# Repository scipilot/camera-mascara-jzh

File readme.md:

This is a Raspberry Pi Hat for the "Camera Mascara" mark 2, containing a photodiode transimpedance amplifier and an ADC with a bunch of breakout options for experimenting with the gain and other parameters, like a dev board.

See the other two related repos: 

- https://github.com/scipilot/camera-mascara			(essential code for running the camera)
- https://github.com/scipilot/camera-mascara-vue-pocketbase 	(optional UI app)

## How to use

The circuit has options, but also fair defaults so you can just plug in a photodiode to J2, jump J4 pins 1-2 and jump J3 pins 1-2. 

The jumper options were intended to facilitate trialling different opamp designs not just passive values, while still using well-soldered SMD components, avoiding breadboard problems. There are many ways to feed a photodiode signal into an opamp, so I wanted to enable radical changes to the circuit - although probably could have done much better with a more open "protoboard" type layout. The default design is a transimpedance amplifier, where the photodiode reverse bias is also generated via the opamp as the negative feedback tries to keep the inverting input the same as the non-inverting input which itself is held at the bias level.

The default Rfb 10MΩ turned out to be too high (for the Hamamatsu diode I tried). But a 1.6MΩ pot on J3 (on pins 4-5, with pins 2-3 jumped) was very useful for various level experiments. Somewhere around 500kΩ is probably a good starting point.

The potentiometer option on J4 turned out not to be so useful, but installing R1 was more useful in setting the reverse bias of the photodiode. It depends on the photodiode, but keeping the bias as low as possible (while still performing its function) helps to keep the "black" output level down lower which was more compatible with the ADC (especially without the VIN-neg bias option) and allowing higher gain before clipping. I installed a 25kΩ R1 which leads to a 1V reverse bias, (25:100 divider of 5V on the Pi supply) which is safely above the 0.7V minimum reverse bias of the Hamamatsu diode.

The 0Ω links were also intended to be removable, but in reality it's pretty difficult at that size!

The opamp capacitors aren't so important these low frequencies - they are in the reference designs which are more concerned with high-frequency applications. Considering this ADC supports 15 to 240 samples per second, it's all running sub 1kHz.

Shielding the cable to the photosensor is important, which can be connected to Pin 1 of J2 and linked to GND. This significantly reduces mains hum, especially with higher amplification of very low light levels (single pixel mask).

The ADS1110 is IC2 addressed according to the variant, so e.g. ADS1110-ED0 is on address 0x48. The ADS1110 does not use registers so some standard tools don't work with it, as they commonly write a register address before reading which will overwrite the config of this chip. 

The ADS1110 has four possible differential ranges: -2V to +2V at PGA (gain) x1, down to -0.25 to +0.25V at PGA gain x8. 

Note: As we are measuring positive going signals (not AC or audio) but the ADC is differential, the input should to biased to the bottom of this range to enable us to use the full range. To do this you can supply 1V or 2V to the negative input. I did not facilitate this option in the first version of the schematic, and sadly routed the VIN-neg pin to the GND under the chip which made it difficult to amend (desolder chip and cut the track or lift the pin)! I have remedied this in v2 of the schematic (not manufactured yet). This bias could also be achieved in the output of the opamp or other ways, but the VIN-neg is the easiest.

TP1 is the most interesting signal to probe. Ensuring it's clean and not going to clip outside the range of the ADC is crucial. 

TP2 isn't really useful, as the signal is a current not voltage.  TP3 was used in experiments to record the PD rev-bias and its effect on the performance.

I added a bunch of other proto-board-like component positions and jumper/vias which are not on the schematic. These were useful to be able to hard-solder optional things like a 1V voltage divider for the VIN-neg ADC input (after cutting the strap to GND).

There were no TPs for the I2C for debugging which was annoying and will also be remedied in v2.

The components I chose were swayed by what was available at JLCPCB (or LCSC). The TIA is good, but I think the ADC could be better.

Next steps: v2 will have the prototyping amendments mentioned, plus possible a triple channel layout, for doing RGB images, or a dual-sensor for monitoring background light levels, and perhaps a different non-differential ADC or with less weird I2C. 

Also I forgot the GO button which could be used to take a picture, but the UI app seems more suitable for this, as there are resolution options and other config available. The GO button might be useful if the device settles down to be a point-and-shoot camera with less focus on endlessly tuning the circuit. At that time, I'd make a "production" board without so many the prototyping options. 

There currently is no case design.

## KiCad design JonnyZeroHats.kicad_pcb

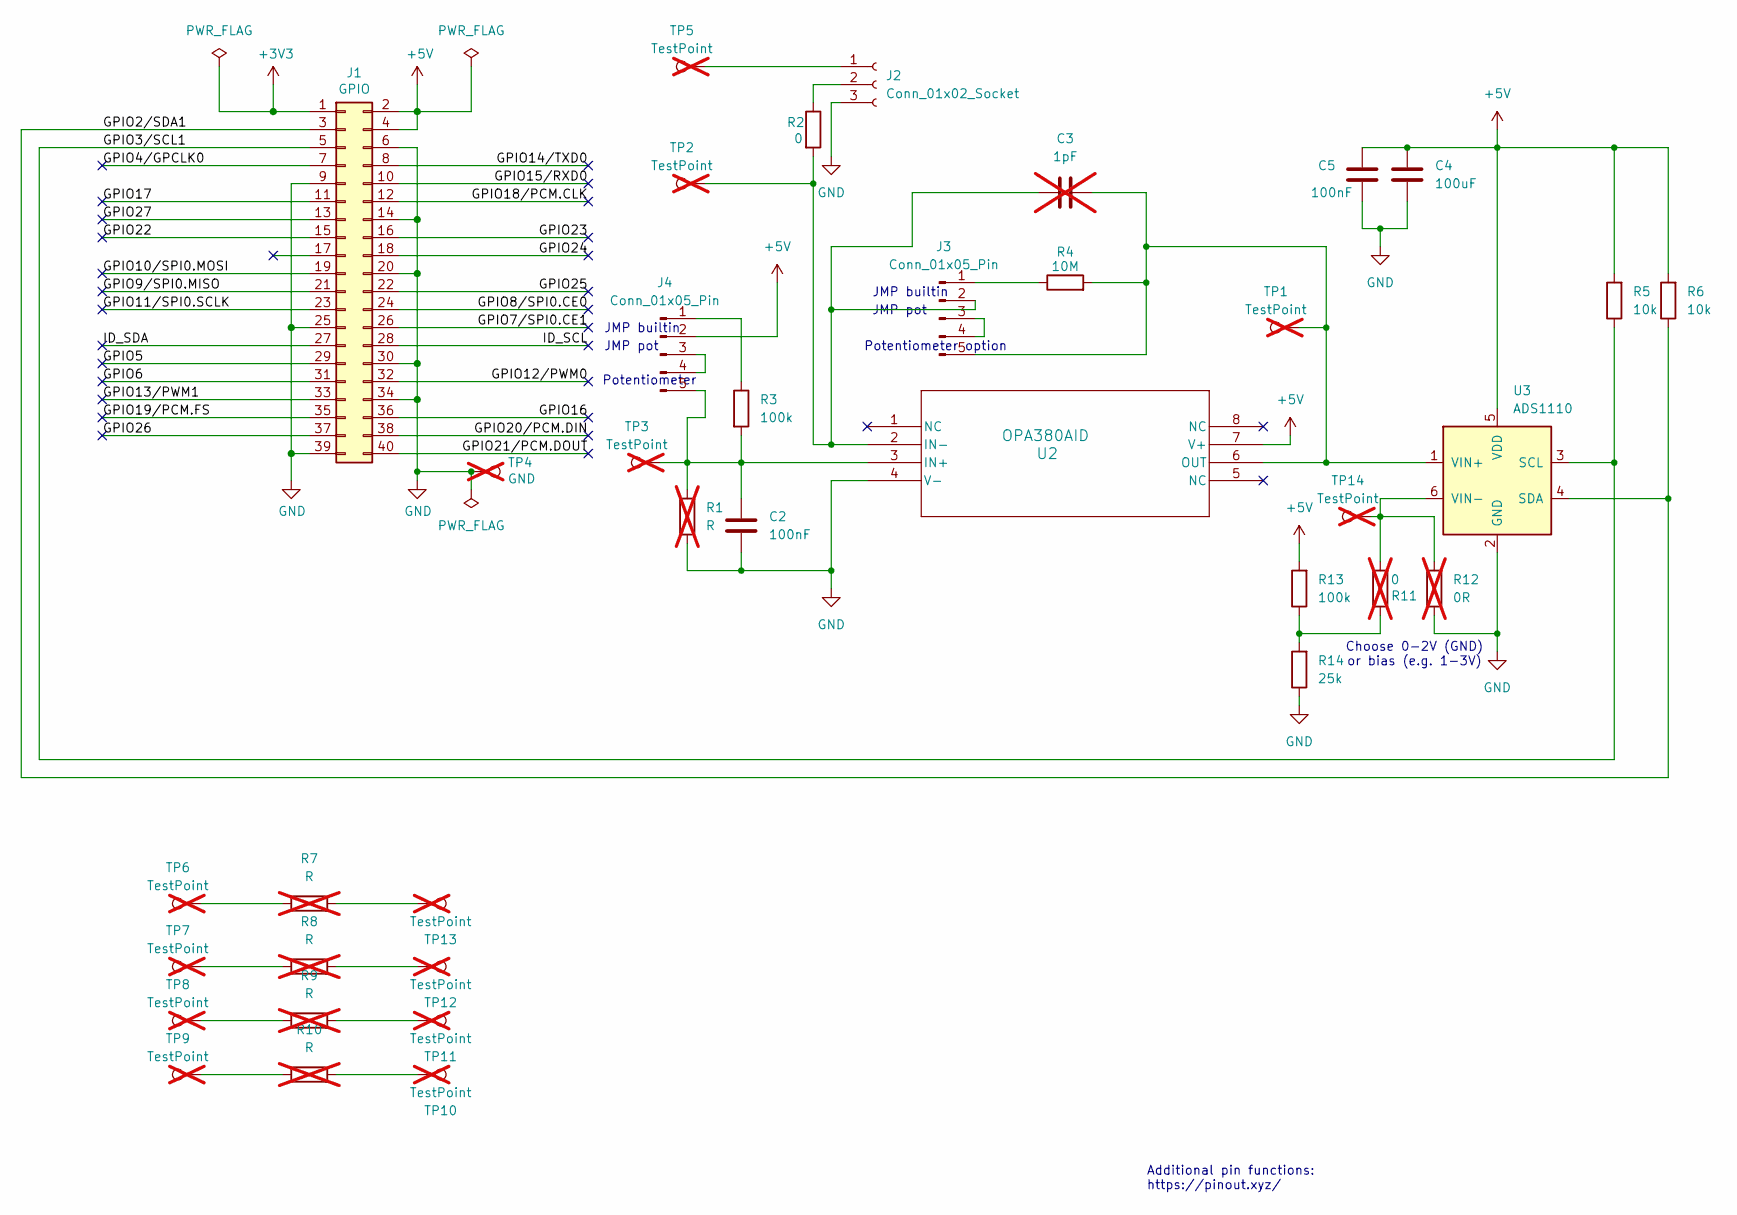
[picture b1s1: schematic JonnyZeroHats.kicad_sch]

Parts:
C2, C5: 100nF; C_1206_3216Metric; LCSC Part # C24497
C3: 1pF; C_Disc_D3.8mm_W2.6mm_P2.50mm; LCSC Part # C1786; not fitted
C4: 100uF; C_1206_3216Metric; LCSC Part # C15008
J1: GPIO; PinSocket_2x20_P2.54mm_Vertical
J2: Conn_01x02_Socket; PinHeader_1x03_P2.54mm_Vertical; LCSC Part # C5445396
J3, J4: Conn_01x05_Pin; PinHeader_1x05_P2.54mm_Vertical; LCSC Part # C225480
R1: R; R_Axial_DIN0204_L3.6mm_D1.6mm_P2.54mm_Vertical; not fitted
R2: 0; R_1206_3216Metric; LCSC Part # C17888
R3: 100k; R_1206_3216Metric; LCSC Part # C17900
R4: 10M; R_1206_3216Metric; LCSC Part # C26119
R5, R6: 10k; R_0805_2012Metric; LCSC Part # C17414
R7, R8, R9, R10: R; R_Axial_DIN0207_L6.3mm_D2.5mm_P10.16mm_Horizontal; not fitted
R11: 0; R_Axial_DIN0207_L6.3mm_D2.5mm_P2.54mm_Vertical; LCSC Part # C17888; not fitted
R12: 0R; R_Axial_DIN0207_L6.3mm_D2.5mm_P2.54mm_Vertical; not fitted
R13: 100k; R_0805_2012Metric; LCSC Part # C17414
R14: 25k; R_0805_2012Metric; LCSC Part # C17414
TP1, TP2, TP3, TP5, TP6, TP7, TP8, TP9, TP10, TP11, TP12, TP13, TP14: TestPoint; TestPoint_THTPad_2.5x2.5mm_Drill1.2mm; not fitted
TP4: GND; TestPoint_THTPad_2.5x2.5mm_Drill1.2mm; not fitted
U2: OPA380AID; D8; LCSC Part # C201677
U3: ADS1110; SOT-23-6; LCSC Part # C16598

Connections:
+3V3: J1.1
+5V: C4.1, C5.1, J1.2, J1.4, J4.2, R5.2, R6.2, R13.2, U2.7 (V+), U3.5 (VDD)
/GPIO2/SDA1: J1.3, R6.1, U3.4 (SDA)
/GPIO3/SCL1: J1.5, R5.1, U3.3 (SCL)
/GPIO4/GPCLK0: J1.7
/GPIO5: J1.29
/GPIO6: J1.31
/GPIO7/SPI0.CE1: J1.26
/GPIO8/SPI0.CE0: J1.24
/GPIO9/SPI0.MISO: J1.21
/GPIO10/SPI0.MOSI: J1.19
/GPIO11/SPI0.SCLK: J1.23
/GPIO12/PWM0: J1.32
/GPIO13/PWM1: J1.33
/GPIO14/TXD0: J1.8
/GPIO15/RXD0: J1.10
/GPIO16: J1.36
/GPIO17: J1.11
/GPIO18/PCM.CLK: J1.12
/GPIO19/PCM.FS: J1.35
/GPIO20/PCM.DIN: J1.38
/GPIO21/PCM.DOUT: J1.40
/GPIO22: J1.15
/GPIO23: J1.16
/GPIO24: J1.18
/GPIO25: J1.22
/GPIO26: J1.37
/GPIO27: J1.13
/ID_SCL: J1.28
/ID_SDA: J1.27
GND: C2.2, C4.2, C5.2, J1.6, J1.9, J1.14, J1.20, J1.25, J1.30, J1.34, J1.39, J2.3, R1.2, R12.1, R14.1, TP4.1, U2.4 (V-), U3.2 (GND)
unnamed: J2.1, TP5.1
unnamed: J2.2, R2.1
unnamed: J3.1, R4.1
unnamed: C3.1, J3.2, R2.2, TP2.1, U2.2 (IN-)
unnamed: J3.3, J3.4
unnamed: C3.2, J3.5, R4.2, TP1.1, U2.6 (OUT), U3.1 (VIN+)
unnamed: J4.1, R3.1
unnamed: J4.3, J4.4
unnamed: C2.1, J4.5, R1.1, R3.2, TP3.1, U2.3 (IN+)
unnamed: R7.1, TP6.1
unnamed: R7.2, TP13.1
unnamed: R8.1, TP7.1
unnamed: R8.2, TP12.1
unnamed: R9.1, TP8.1
unnamed: R9.2, TP11.1
unnamed: R10.1, TP9.1
unnamed: R10.2, TP10.1
unnamed: R11.1, R13.1, R14.2
unnamed: R11.2, R12.2, TP14.1, U3.6 (VIN-)

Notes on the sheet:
JMP pot
Potentiometer
Choose 0-2V (GND) or bias (e.g. 1-3V)
Potentiometer option
JMP builtin
Additional pin functions: https://pinout.xyz/

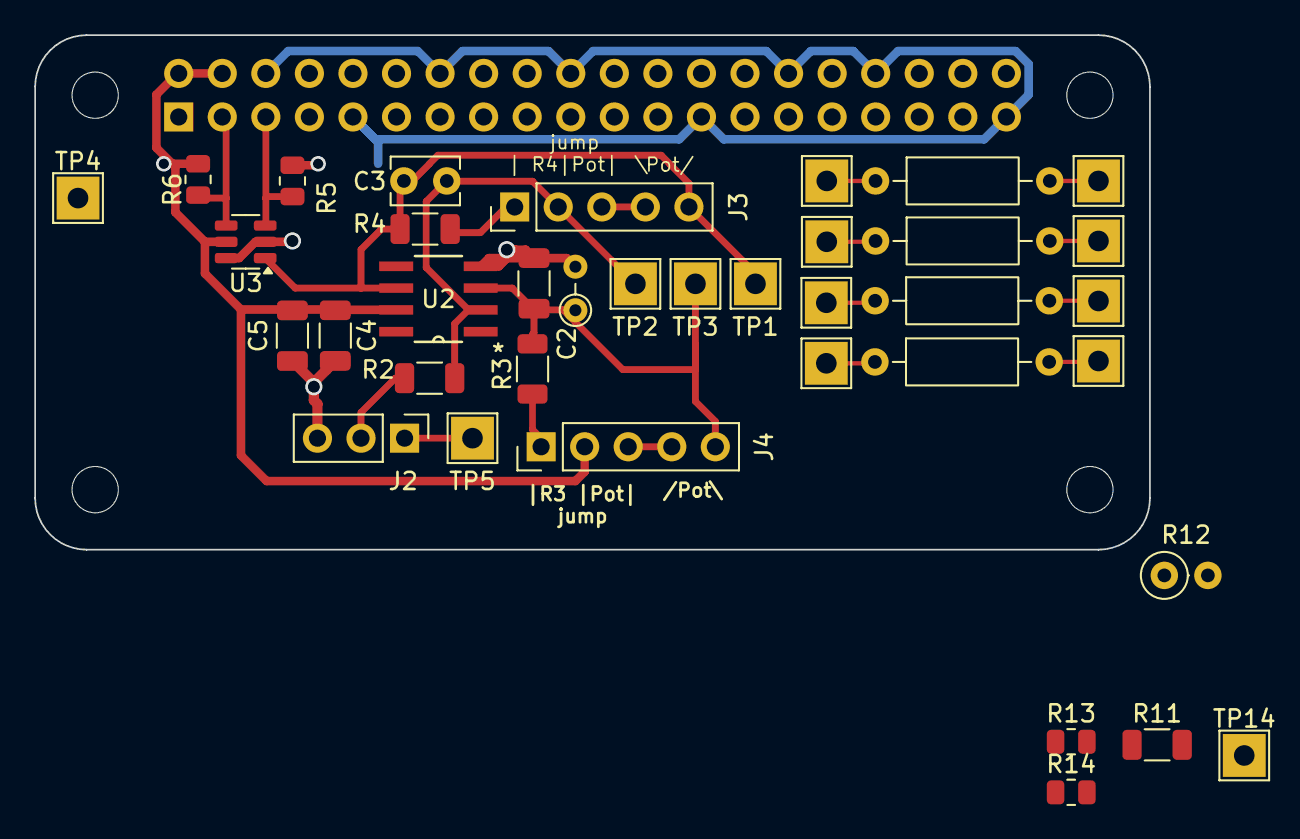
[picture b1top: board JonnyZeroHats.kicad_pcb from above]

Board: 2 copper layers, 65.0 x 30.0 mm, 42 parts (1 on the bottom side), 23 nets.

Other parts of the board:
MH1, MH2, MH3, MH4: MountingHole_2.7mm_M2.5

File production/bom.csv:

Designator,Footprint,Quantity,Value,LCSC Part #
"C2, C5",1206,2,100nF,C24497
C4,1206,1,100uF,C15008
J1,PinSocket_2x20_P2.54mm_Vertical,1,GPIO,
J2,PinHeader_1x03_P2.54mm_Vertical,1,Conn_01x02_Socket,C5445396
"J3, J4",PinHeader_1x05_P2.54mm_Vertical,2,Conn_01x05_Pin,C225480
R2,1206,1,0,C17888
R3,1206,1,100k,C17900
R4,1206,1,10M,C26119
"R5, R6",0805,2,10k,C17414
U2,D8,1,OPA380AID,C201677
U3,SOT-23-6,1,ADS1110,C16598

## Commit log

2025-11-17 initialise
2025-11-17 Readme
2025-11-17 docs
